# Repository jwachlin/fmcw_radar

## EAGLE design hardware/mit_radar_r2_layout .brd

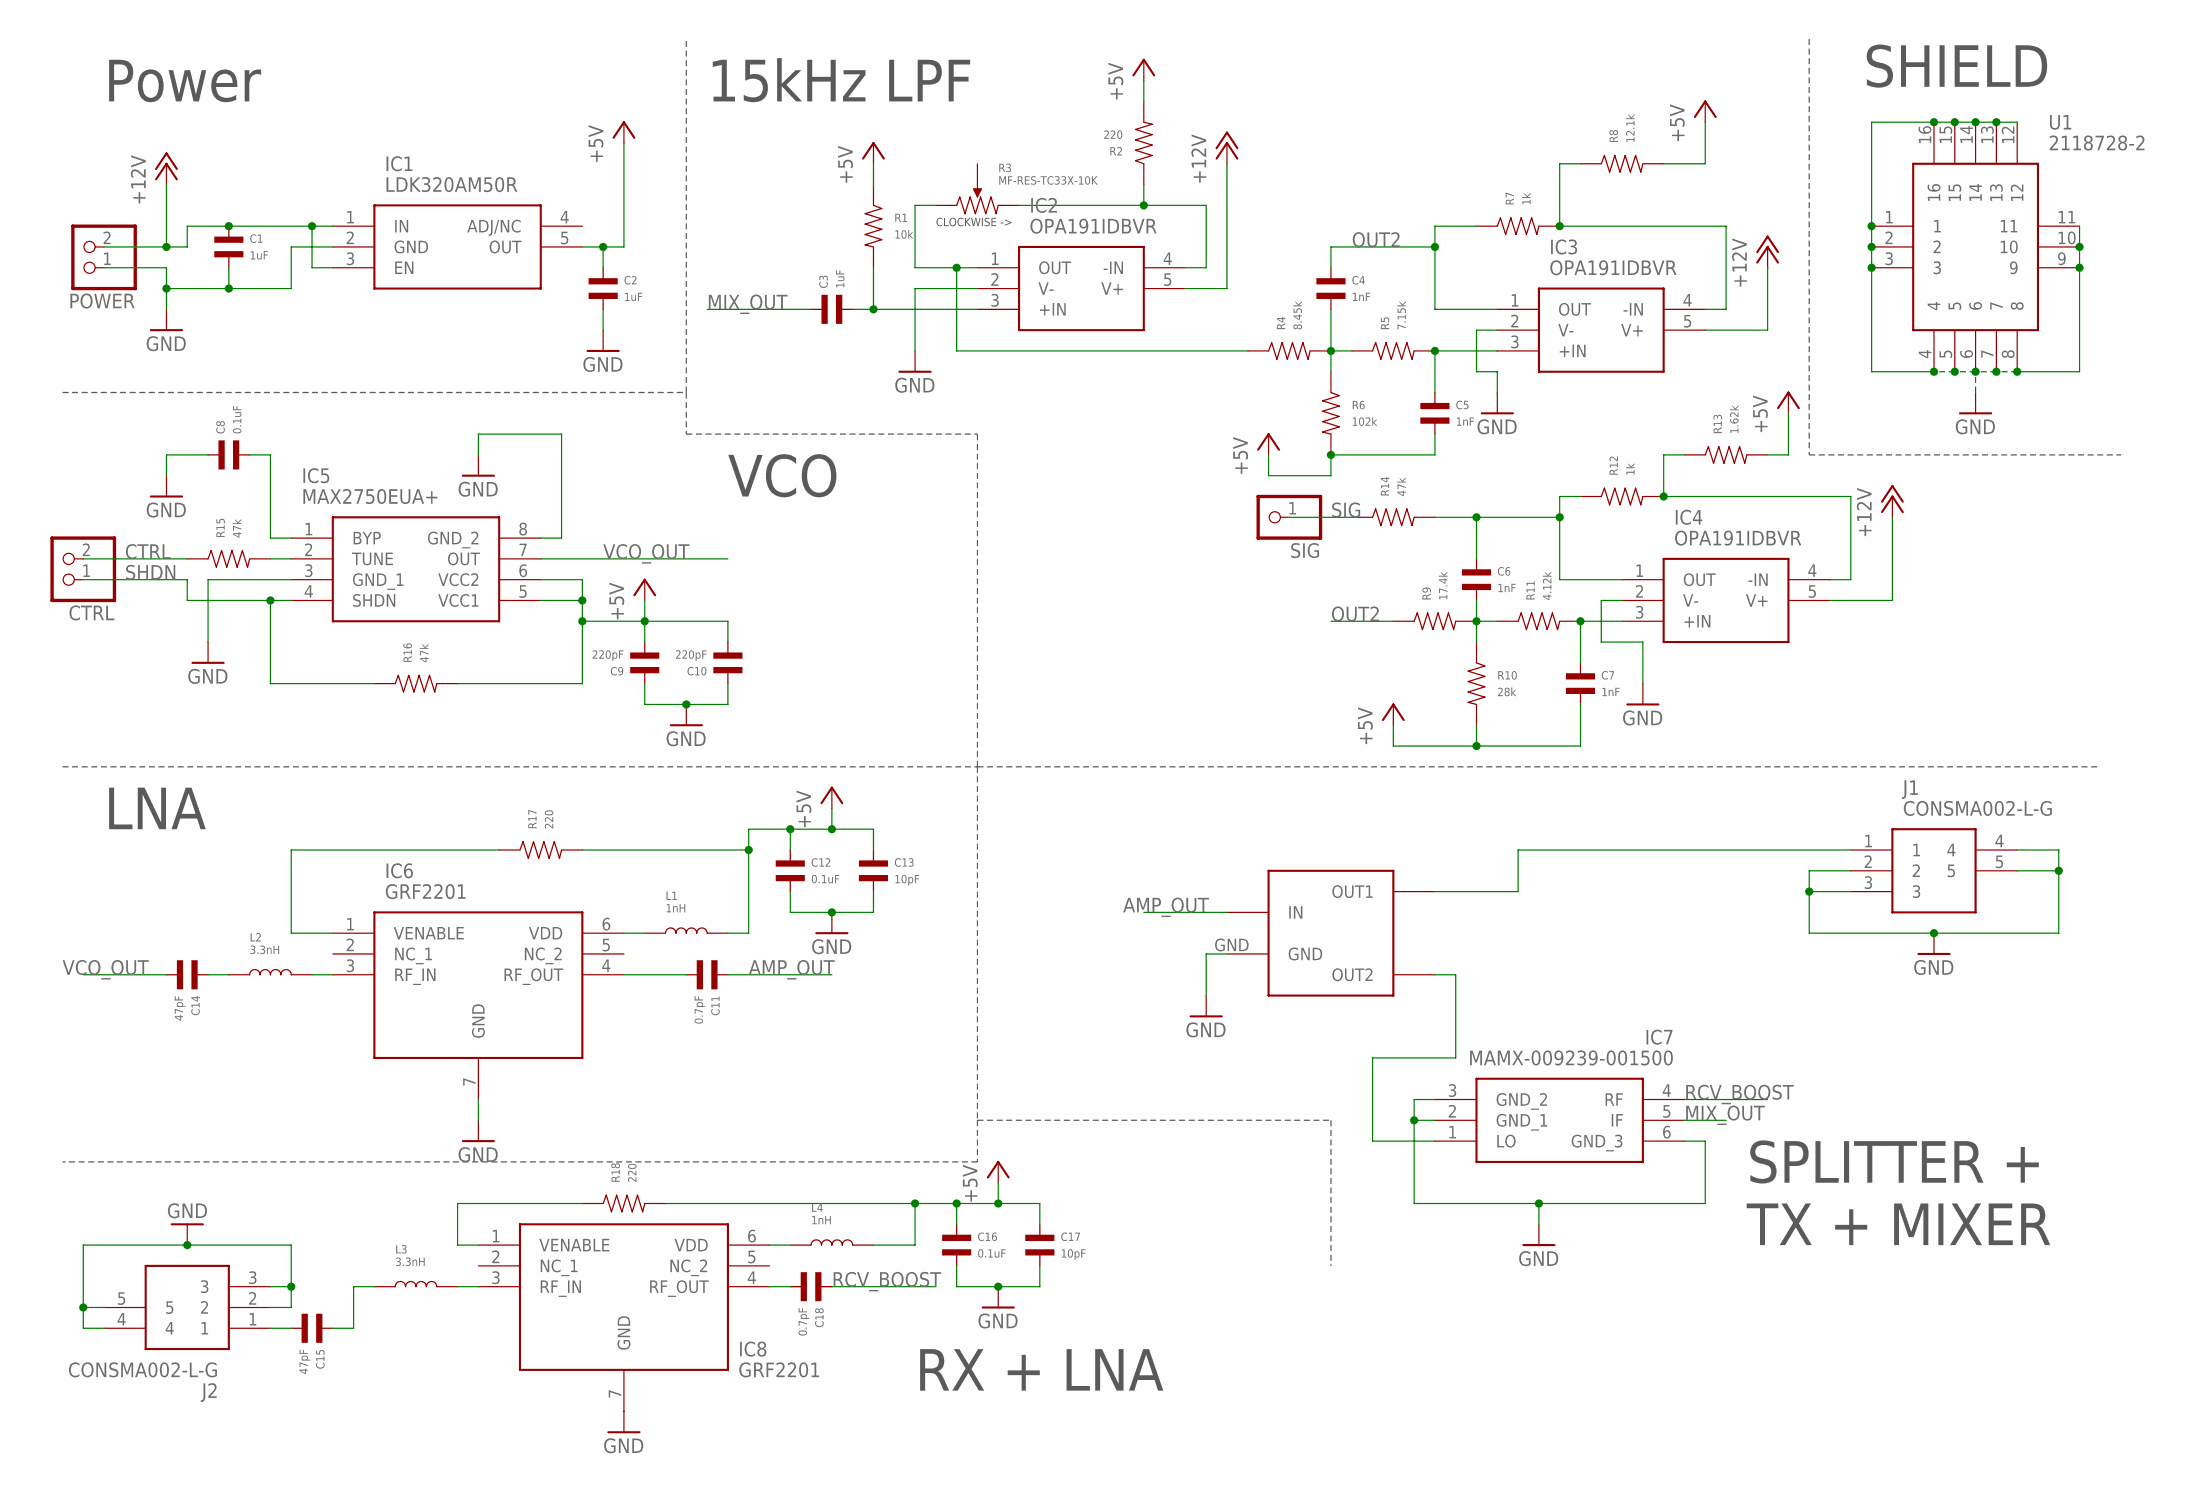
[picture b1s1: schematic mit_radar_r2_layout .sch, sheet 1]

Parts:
C1, C2, C3: 1uF; C0402
C4, C5, C6, C7: 1nF; C0402
C8, C12, C16: 0.1uF; C0402
C9, C10: 220pF; C0402
C11, C18: 0.7pF; C0402
C13, C17: 10pF; C0402
C14, C15: 47pF; C0402
CTRL: PINHD-1X2; 1X02
IC1: LDK320AM50R; SOT95P280X145-5N
IC2, IC3, IC4: OPA191IDBVR; SOT95P280X145-5N
IC5: MAX2750EUA+; SOP65P490X110-8N
IC6, IC8: GRF2201; SON50P150X150X50-7N
IC7: MAMX-009239-001500; MAMX009239001500
J1, J2: CONSMA002-L-G; CONSMA002LG
L1, L4: 1nH; L0402
L2, L3: 3.3nH; L0402
POWER: PINHD-1X2; 1X02
R1: 10k; R0402
R2, R17, R18: 220; R0402
R3: MF-RES-TC33X-10K; TC33
R4: 8.45k; R0402
R5: 7.15k; R0402
R6: 102k; R0402
R7, R12: 1k; R0402
R8: 12.1k; R0402
R9: 17.4k; R0402
R10: 28k; R0402
R11: 4.12k; R0402
R13: 1.62k; R0402
R14, R15, R16: 47k; R0402
SIG: PINHD-1X1; 1X01
U1: 2118728-2; 21187282
U$1: PS3216GT2-R50-T1

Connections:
+5V: C2.P$1, C5.P$2, C7.P$2, C9.P$2, C10.P$2, C12.P$1, C13.P$1, C16.P$1, C17.P$1, IC1.5 (OUT), IC5.5 (VCC1), IC5.6 (VCC2), L1.P$2, L4.P$2, R1.P$1, R2.P$2, R6.P$2, R8.P$2, R10.P$2, R13.P$2, R16.P$2, R17.P$2, R18.P$2
+12V: C1.P$1, IC1.1 (IN), IC1.3 (EN), IC2.5 (V+), IC3.5 (V+), IC4.5 (V+), POWER.2
AMP_OUT: C11.P$1, U$1.IN
CTRL: CTRL.2, R15.P$1; also elsewhere on the board
GND: C1.P$2, C2.P$2, C8.P$1, C9.P$1, C10.P$1, C12.P$2, C13.P$2, C16.P$2, C17.P$2, IC1.2 (GND), IC2.2 (V-), IC3.2 (V-), IC4.2 (V-), IC5.3 (GND_1), IC5.8 (GND_2), IC6.7 (GND), IC7.2 (GND_1), IC7.3 (GND_2), IC7.6 (GND_3), IC8.7 (GND), J1.2, J1.3, J1.4, J1.5, J2.2, J2.3, J2.4, J2.5, POWER.1, U1.1, U1.2, U1.3, U1.4, U1.5, U1.6, U1.7, U1.8, U1.9, U1.10, U1.11, U1.12, U1.13, U1.14, U1.15, U1.16, U$1.GND; also elsewhere on the board
MIX_OUT: C3.P$1, IC7.5 (IF)
unnamed: C3.P$2, IC2.3 (+IN), R1.P$2
unnamed: IC2.4 (-IN), R2.P$1, R3.P$3
unnamed: IC2.1 (OUT), R3.P$1, R4.P$1
unnamed: C4.P$2, R4.P$2, R5.P$1, R6.P$1
unnamed: C5.P$1, IC3.3 (+IN), R5.P$2
unnamed: C6.P$2, R9.P$2, R10.P$1, R11.P$1
unnamed: C7.P$1, IC4.3 (+IN), R11.P$2
unnamed: IC3.4 (-IN), R7.P$2, R8.P$1
unnamed: C6.P$1, IC4.1 (OUT), R12.P$1, R14.P$2
unnamed: IC4.4 (-IN), R12.P$2, R13.P$1
unnamed: IC5.2 (TUNE), R15.P$2
unnamed: C8.P$2, IC5.1 (BYP)
unnamed: C11.P$2, IC6.4 (RF_OUT)
unnamed: IC6.6 (VDD), L1.P$1
unnamed: IC6.1 (VENABLE), R17.P$1
unnamed: IC6.3 (RF_IN), L2.P$2
unnamed: C14.P$1, L2.P$1
unnamed: IC8.6 (VDD), L4.P$1
unnamed: J1.1, U$1.OUT1
unnamed: IC7.1 (LO), U$1.OUT2
unnamed: C15.P$1, L3.P$1
unnamed: C15.P$2, J2.1
unnamed: IC8.3 (RF_IN), L3.P$2
unnamed: IC8.1 (VENABLE), R18.P$1
unnamed: C18.P$2, IC8.4 (RF_OUT)
OUT2: C4.P$1, IC3.1 (OUT), R7.P$1, R9.P$1
RCV_BOOST: C18.P$1, IC7.4 (RF)
SHDN: CTRL.1, IC5.4 (SHDN), R16.P$1; also elsewhere on the board
SIG: R14.P$1, SIG.1; also elsewhere on the board
VCO_OUT: C14.P$2, IC5.7 (OUT)

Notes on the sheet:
Power
15kHz LPF
VCO
SHIELD
LNA
RX + LNA
SPLITTER + TX + MIXER

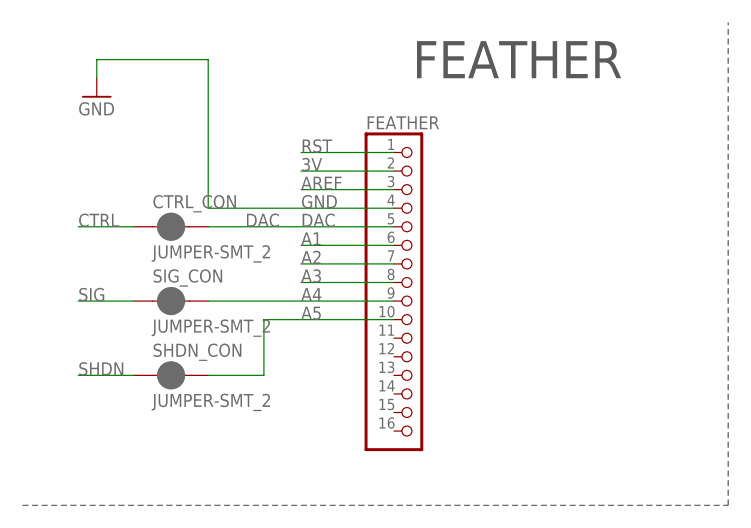
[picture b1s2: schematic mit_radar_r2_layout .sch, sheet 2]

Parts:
CTRL_CON: JUMPER-SMT_2; SMT-JUMPER_2_NC_PASTE_NO-SILK
FEATHER: PINHD-1X16; 1X16
SHDN_CON: JUMPER-SMT_2; SMT-JUMPER_2_NC_PASTE_NO-SILK
SIG_CON: JUMPER-SMT_2; SMT-JUMPER_2_NC_PASTE_NO-SILK

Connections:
3V: FEATHER.2
A1: FEATHER.6
A2: FEATHER.7
A3: FEATHER.8
A4: FEATHER.9, SIG_CON.2
A5: FEATHER.10, SHDN_CON.2
AREF: FEATHER.3
CTRL: CTRL_CON.1; also elsewhere on the board
DAC: CTRL_CON.2, FEATHER.5
GND: FEATHER.4; also elsewhere on the board
RST: FEATHER.1
SHDN: SHDN_CON.1; also elsewhere on the board
SIG: SIG_CON.1; also elsewhere on the board

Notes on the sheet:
FEATHER

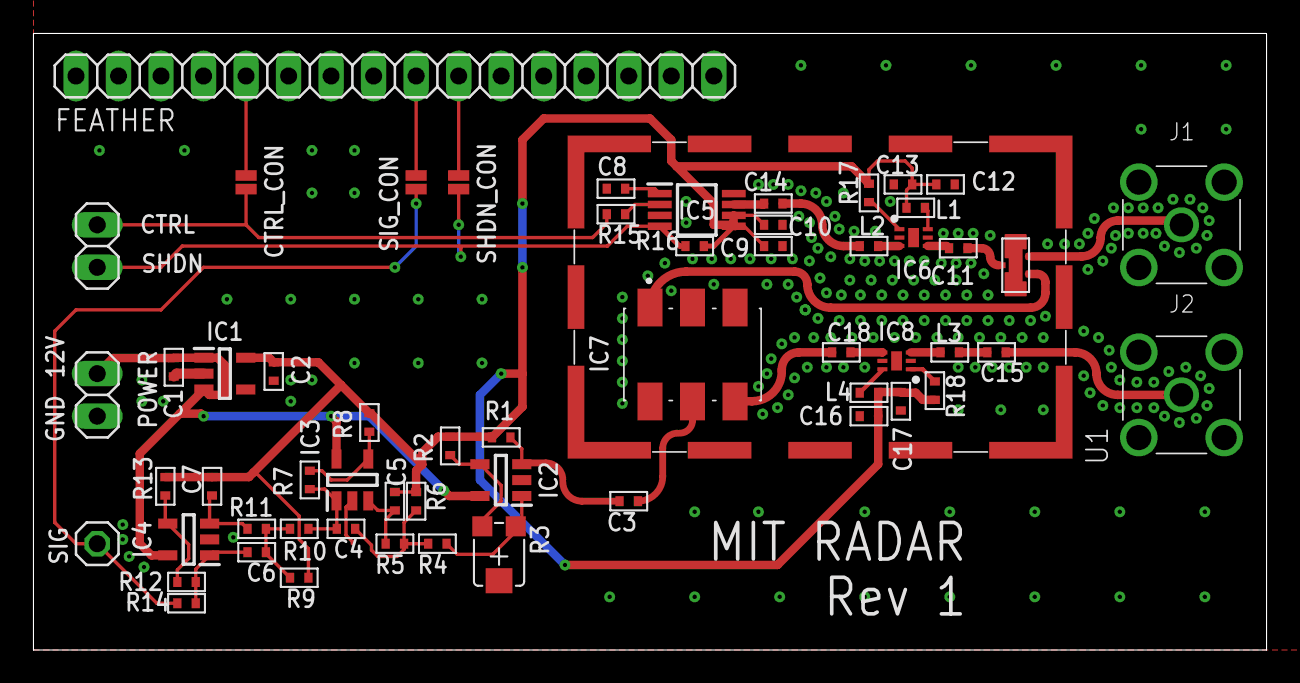
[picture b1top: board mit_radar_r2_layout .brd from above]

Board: 2 copper layers, 73.7 x 36.8 mm, 59 parts (0 on the bottom side), 39 nets.

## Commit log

2020-03-14 Adds revision 2 design

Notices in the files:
parts and their libraries:
SparkFun-Jumpers: Licensing: Creative Commons ShareAlike 4.0 International - https://creativecommons.org/licenses/by-sa/4.0
